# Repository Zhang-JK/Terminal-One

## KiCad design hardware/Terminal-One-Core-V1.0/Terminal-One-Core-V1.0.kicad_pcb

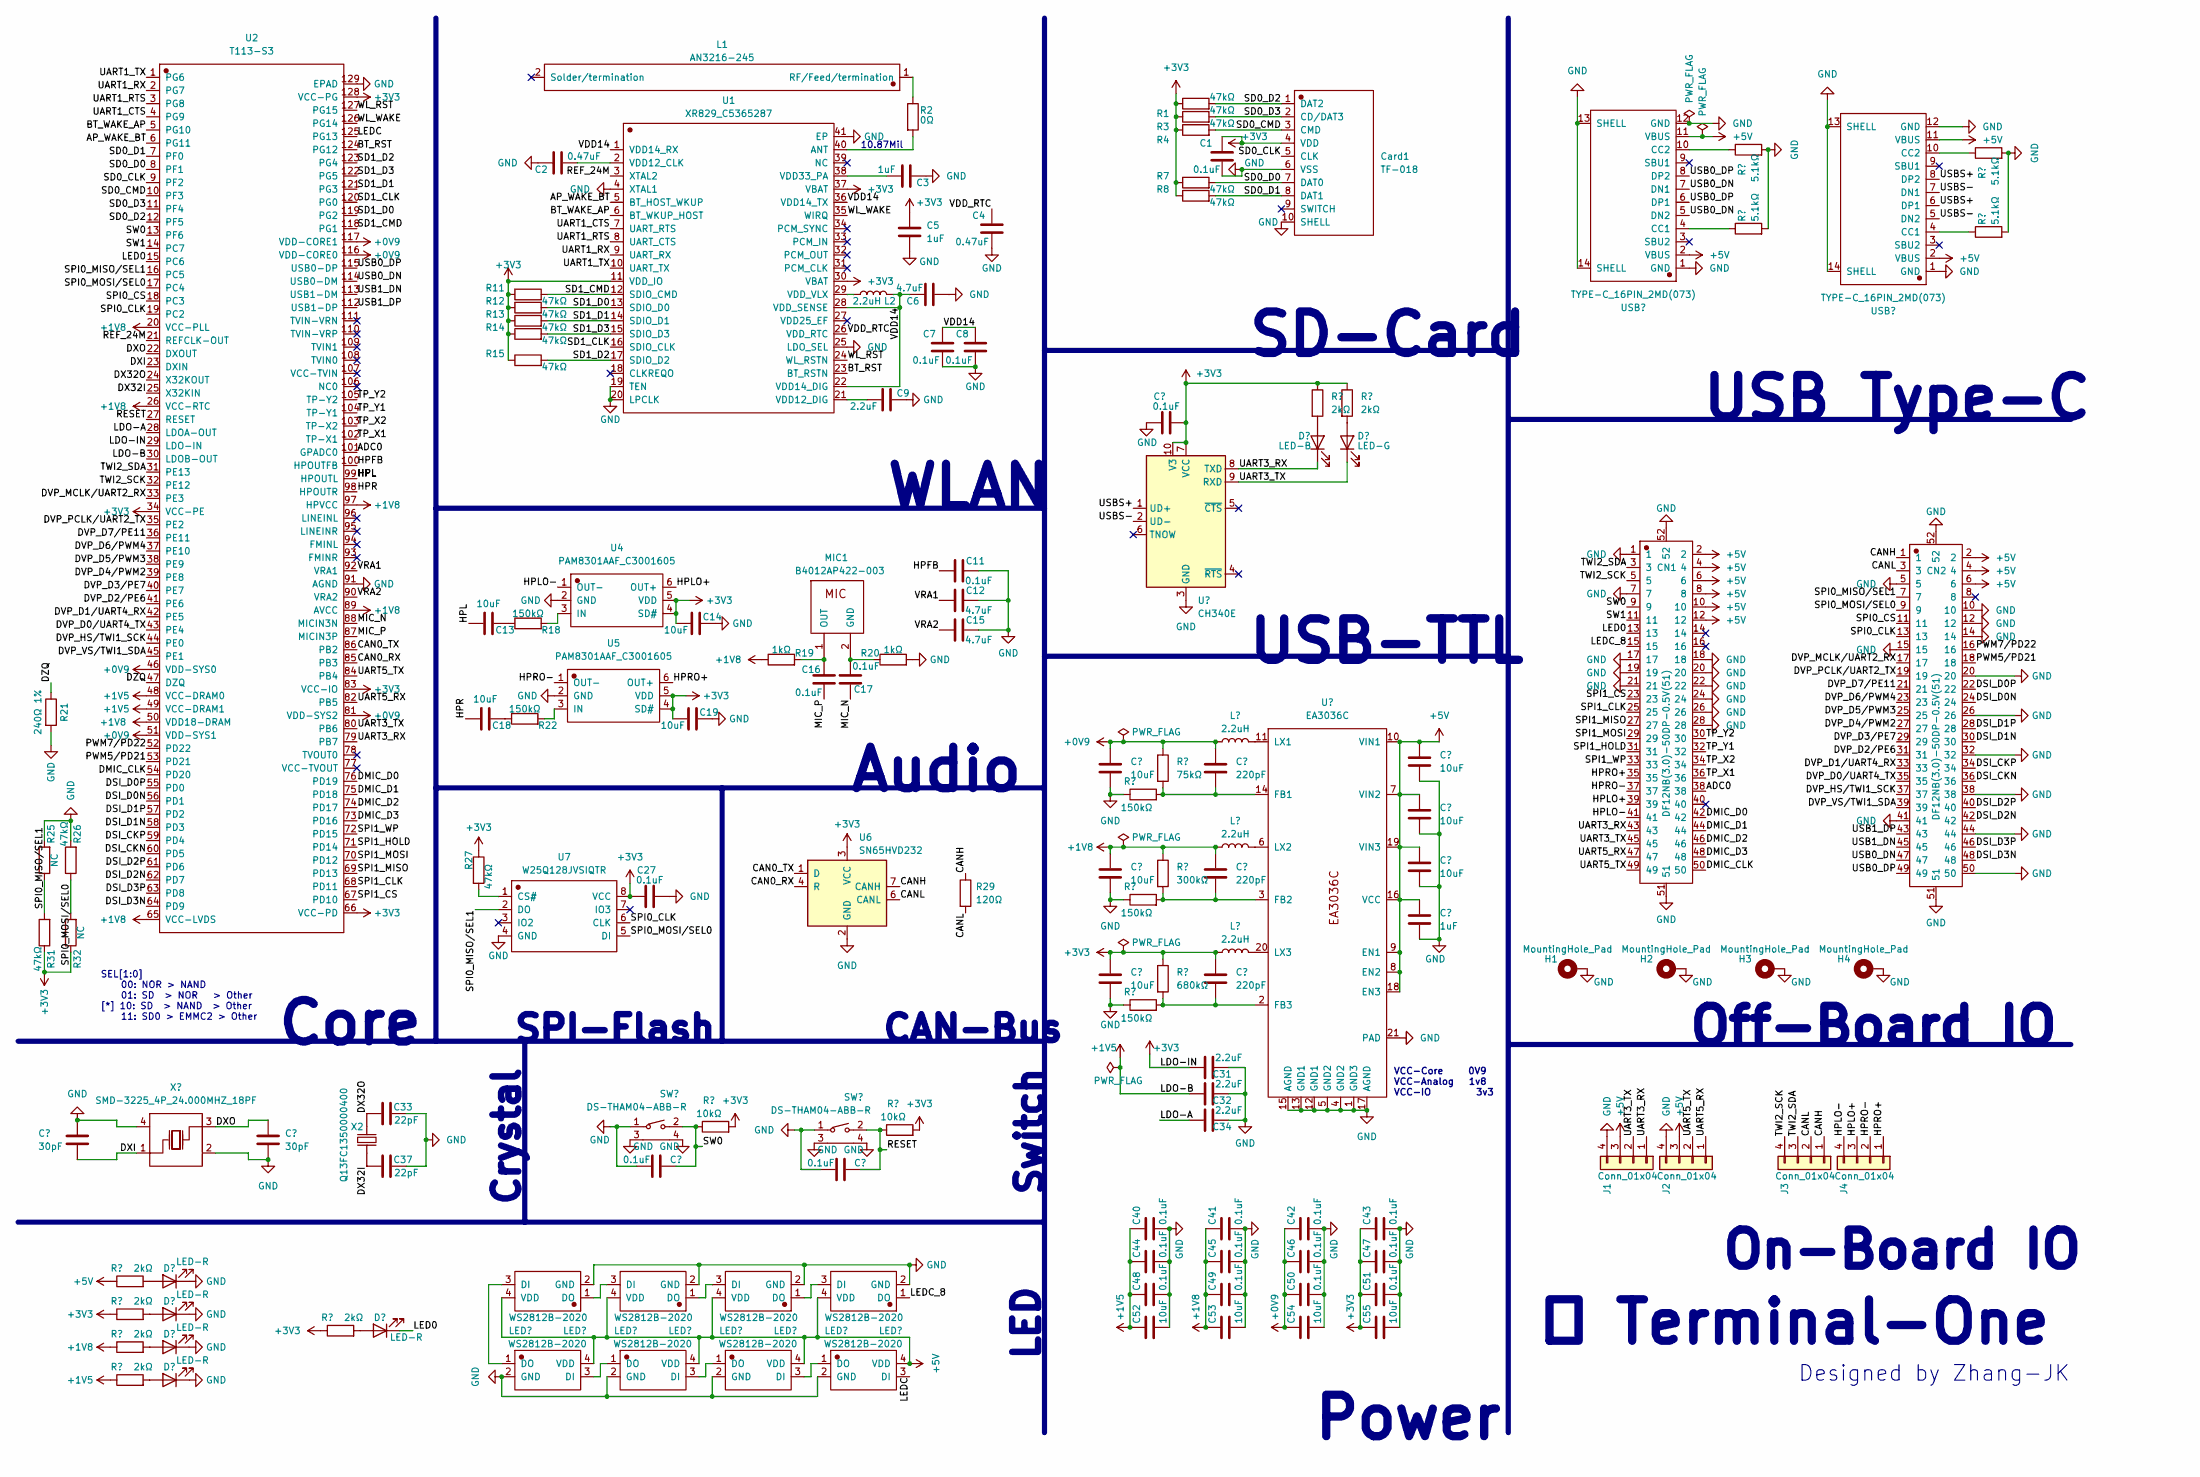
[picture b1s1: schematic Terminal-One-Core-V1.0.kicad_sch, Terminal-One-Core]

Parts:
C1, C7, C8, C10, C11, C16, C17, C27, C38, C39, C40, C41, C42, C43, C44, C45, C46, C47, C48, C49, C50, C51: 0.1uF; C_0402_1005Metric
C2, C4: 0.47uF; C_0402_1005Metric
C3, C5, C28: 1uF; C_0402_1005Metric
C6, C12, C15: 4.7uF; C_0603_1608Metric
C9, C31, C32, C34: 2.2uF; C_0603_1608Metric
C13, C14, C18, C19, C20, C23, C24, C52, C53, C54, C55: 10uF; C_0603_1608Metric
C21, C25, C29: 10uF; C_0805_2012Metric
C22, C26, C30: 220pF; C_0603_1608Metric
C33, C37: 22pF; C_0402_1005Metric
C35, C36: 30pF; C_0402_1005Metric
CN1, CN2: DF12NB(3.0)-50DP-0.5V(51); CONN-SMD_50P-P0.50_DF12NB3.0-50DP-0.5V-51
Card1: TF-018; TF-SMD_TF-018
D1: LED-B; LED_0603_1608Metric
D2: LED-G; LED_0603_1608Metric
D3, D4, D5, D6, D7: LED-R; LED_0603_1608Metric
H1, H2, H3, H4: MountingHole_Pad; MountingHole_2.7mm_M2.5_ISO14580_Pad_TopOnly
J1, J2, J3, J4: Conn_01x04; JST_GH_BM04B-GHS-TBT_1x04-1MP_P1.25mm_Vertical
L1: AN3216-245; ANT-SMD_L3.2-W1.6-A
L2, L3, L4, L5: 2.2uH; L_0805_2012Metric
LED1, LED2, LED3, LED4, LED5, LED6, LED7, LED8: WS2812B-2020; LED-SMD_4P-L2.0-W2.0-TL_WS2812B-2020
MIC1: B4012AP422-003; MIC-TH_BD4.0-P1.40-D0.3-L
R1, R3, R4, R7, R8, R11, R12, R13, R14, R15, R26, R27, R31: 47kΩ; R_0402_1005Metric
R2: 0Ω; R_0402_1005Metric
R5, R6, R9, R10: 5.1kΩ; R_0402_1005Metric
R16, R17, R37, R38, R39, R40, R41: 2kΩ; R_0402_1005Metric
R18, R22, R24, R30, R34: 150kΩ; R_0402_1005Metric
R19, R20: 1kΩ; R_0402_1005Metric
R21: 240Ω 1%; R_0402_1005Metric
R23: 75kΩ; R_0402_1005Metric
R25, R32: NC; R_0402_1005Metric
R28: 300kΩ; R_0402_1005Metric
R29: 120Ω; R_0402_1005Metric
R33: 680kΩ; R_0402_1005Metric
R35, R36: 10kΩ; R_0402_1005Metric
SW1, SW2: DS-THAM04-ABB-R; SW-SMD_D-SWITCH_DS-THAM04-ABB-R
U1: XR829_C5365287; QFN-40_L5.0-W5.0-P0.40-BL-EP3.4
U2: T113-S3; TQFP-128_L14.0-W14.0-P0.40-LS16.0-BL-EP6.4
U3: CH340E; MSOP-10_3x3mm_P0.5mm
U4, U5: PAM8301AAF_C3001605; SOT-23-6_L2.9-W1.6-P0.95-LS2.8-BR
U6: SN65HVD232; SOIC-8_3.9x4.9mm_P1.27mm
U7: W25Q128JVSIQTR; SOIC-8_L5.3-W5.3-P1.27-LS8.0-BL
U8: EA3036C; WQFN-20-1EP_3x3mm_P0.4mm_EP1.7x1.7mm_ThermalVias
USB1, USB2: TYPE-C_16PIN_2MD(073); USB-C-SMD_TYPE-C-6PIN-2MD-073
X1: SMD-3225_4P_24.000MHZ_18PF; CRYSTAL-SMD_4P-L3.2-W2.5-BL
X2: Q13FC1350000400; FC-135R_L3.2-W1.5

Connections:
+0V9: C21.1, C22.1, C42.1, C46.1, C50.1, C54.1, L3.1, R23.1, U2.46 (VDD-SYS0), U2.51 (VDD-SYS1), U2.81 (VDD-SYS2), U2.116 (VDD-CORE0), U2.117 (VDD-CORE1); also elsewhere on the board
+1V5: C32.1, C40.1, C44.1, C48.1, C52.1, R41.1, U2.30 (LDOB-OUT), U2.48 (VCC-DRAM0), U2.49 (VCC-DRAM1); also elsewhere on the board
+1V8: C25.1, C26.1, C41.1, C45.1, C49.1, C53.1, L4.1, R19.1, R28.1, R40.1, U2.20 (VCC-PLL), U2.26 (VCC-RTC), U2.50 (VDD18-DRAM), U2.65 (VCC-LVDS), U2.89 (AVCC), U2.97 (HPVCC); also elsewhere on the board
+3V3: C1.1, C5.1, C10.2, C14.1, C19.1, C27.1, C29.1, C30.1, C31.1, C43.1, C47.1, C51.1, C55.1, Card1.4 (VDD), L5.1, R1.1, R3.1, R4.1, R7.1, R8.1, R11.1, R12.1, R13.1, R14.1, R15.1, R16.1, R17.1, R27.1, R31.1, R32.1, R33.1, R35.2, R36.2, R38.1, R39.1, U1.11 (VDD_IO), U1.30 (VBAT), U1.37 (VBAT), U2.29 (LDO-IN), U2.34 (VCC-PE), U2.66 (VCC-PD), U2.83 (VCC-IO), U2.128 (VCC-PG), U3.7 (VCC), U3.10 (V3), U4.4 (SD#), U4.5 (VDD), U5.4 (SD#), U5.5 (VDD), U6.3 (VCC), U7.8 (VCC); also elsewhere on the board
+5V: C20.1, C23.1, C24.1, C28.1, CN1.2, CN1.4, CN1.6, CN1.8, CN1.10, CN1.12, CN2.2, CN2.4, CN2.6, J1.3, J2.3, LED1.4 (VDD), LED2.4 (VDD), LED3.4 (VDD), LED4.4 (VDD), LED5.4 (VDD), LED6.4 (VDD), LED7.4 (VDD), LED8.4 (VDD), R37.1, U8.7 (VIN2), U8.8 (EN2), U8.9 (EN1), U8.10 (VIN1), U8.16 (VCC), U8.18 (EN3), U8.19 (VIN3), USB1.2 (VBUS), USB1.11 (VBUS), USB2.2 (VBUS), USB2.11 (VBUS)
/ADC0: CN1.38, U2.101 (GPADC0); also elsewhere on the board
/AP_WAKE_BT: U1.5 (BT_HOST_WKUP), U2.6 (PG11); also elsewhere on the board
/BT_RST: U1.23 (BT_RSTN), U2.124 (PG12); also elsewhere on the board
/BT_WAKE_AP: U1.6 (BT_WKUP_HOST), U2.5 (PG10); also elsewhere on the board
/CAN0_RX: U2.85 (PB3), U6.4 (R); also elsewhere on the board
/CAN0_TX: U2.86 (PB2), U6.1 (D); also elsewhere on the board
/CANH: CN2.1, J3.1, R29.1, U6.7 (CANH)
/CANL: CN2.3, J3.2, R29.2, U6.6 (CANL)
/DMIC_CLK: CN1.50, U2.54 (PD20); also elsewhere on the board
/DMIC_D0: CN1.42, U2.76 (PD19); also elsewhere on the board
/DMIC_D1: CN1.44, U2.75 (PD18); also elsewhere on the board
/DMIC_D2: CN1.46, U2.74 (PD17); also elsewhere on the board
/DMIC_D3: CN1.48, U2.73 (PD16); also elsewhere on the board
/DSI_CKN: CN2.36, U2.60 (PD5); also elsewhere on the board
/DSI_CKP: CN2.34, U2.59 (PD4); also elsewhere on the board
/DSI_D0N: CN2.24, U2.56 (PD1); also elsewhere on the board
/DSI_D0P: CN2.22, U2.55 (PD0); also elsewhere on the board
/DSI_D1N: CN2.30, U2.58 (PD3); also elsewhere on the board
/DSI_D1P: CN2.28, U2.57 (PD2); also elsewhere on the board
/DSI_D2N: CN2.42, U2.62 (PD7); also elsewhere on the board
/DSI_D2P: CN2.40, U2.61 (PD6); also elsewhere on the board
/DSI_D3N: CN2.48, U2.64 (PD9); also elsewhere on the board
/DSI_D3P: CN2.46, U2.63 (PD8); also elsewhere on the board
/DVP_D0/UART4_TX: CN2.35, U2.43 (PE4); also elsewhere on the board
/DVP_D1/UART4_RX: CN2.33, U2.42 (PE5); also elsewhere on the board
/DVP_D2/PE6: CN2.31, U2.41 (PE6); also elsewhere on the board
/DVP_D3/PE7: CN2.29, U2.40 (PE7); also elsewhere on the board
/DVP_D4/PWM2: CN2.27, U2.39 (PE8); also elsewhere on the board
/DVP_D5/PWM3: CN2.25, U2.38 (PE9); also elsewhere on the board
/DVP_D6/PWM4: CN2.23, U2.37 (PE10); also elsewhere on the board
/DVP_D7/PE11: CN2.21, U2.36 (PE11); also elsewhere on the board
/DVP_HS/TWI1_SCK: CN2.37, U2.44 (PE0); also elsewhere on the board
/DVP_MCLK/UART2_RX: CN2.17, U2.33 (PE3); also elsewhere on the board
/DVP_PCLK/UART2_TX: CN2.19, U2.35 (PE2); also elsewhere on the board
/DVP_VS/TWI1_SDA: CN2.39, U2.45 (PE1); also elsewhere on the board
/DX32I: C37.1, U2.25 (X32KIN), X2.1; also elsewhere on the board
/DX32O: C33.1, U2.24 (X32KOUT), X2.2; also elsewhere on the board
/DXI: C35.2, U2.23 (DXIN), X1.1 (OSC1); also elsewhere on the board
/DXO: C36.1, U2.22 (DXOUT), X1.3 (OSC2); also elsewhere on the board
/DZQ: R21.1, U2.47 (DZQ); also elsewhere on the board
/HPFB: C11.1, U2.100 (HPOUTFB); also elsewhere on the board
/HPL: C13.2, U2.99 (HPOUTL); also elsewhere on the board
/HPLO+: CN1.39, J4.3, U4.6 (OUT+)
/HPLO-: CN1.41, J4.4, U4.1 (OUT-)
/HPR: C18.2, U2.98 (HPOUTR); also elsewhere on the board
/HPRO+: CN1.35, J4.1, U5.6 (OUT+)
/HPRO-: CN1.37, J4.2, U5.1 (OUT-)
/LDO-A: C34.1, U2.28 (LDOA-OUT); also elsewhere on the board
/LED0: CN1.13, D5.1 (K), U2.15 (PC6); also elsewhere on the board
/LEDC: LED8.3 (DI), U2.125 (PG13); also elsewhere on the board
/LEDC_8: CN1.15, LED4.1 (DO)
/MIC_N: C17.2, U2.88 (MICIN3N); also elsewhere on the board
/MIC_P: C16.1, U2.87 (MICIN3P); also elsewhere on the board
/PWM5/PD21: CN2.18, U2.53 (PD21); also elsewhere on the board
/PWM7/PD22: CN2.16, U2.52 (PD22); also elsewhere on the board
/REF_24M: U1.3 (XTAL2), U2.21 (REFCLK-OUT); also elsewhere on the board
/RESET: C39.2, R36.1, SW2.2, U2.27 (RESET); also elsewhere on the board
/SD0_CLK: Card1.5 (CLK), U2.9 (PF2); also elsewhere on the board
/SD0_CMD: Card1.3 (CMD), R4.2, U2.10 (PF3); also elsewhere on the board
/SD0_D0: Card1.7 (DAT0), R7.2, U2.8 (PF1); also elsewhere on the board
/SD0_D1: Card1.8 (DAT1), R8.2, U2.7 (PF0); also elsewhere on the board
/SD0_D2: Card1.1 (DAT2), R1.2, U2.12 (PF5); also elsewhere on the board
/SD0_D3: Card1.2 (CD/DAT3), R3.2, U2.11 (PF4); also elsewhere on the board
/SD1_CLK: U1.16 (SDIO_CLK), U2.120 (PG0); also elsewhere on the board
/SD1_CMD: R11.2, U1.12 (SDIO_CMD), U2.118 (PG1); also elsewhere on the board
/SD1_D0: R12.2, U1.13 (SDIO_D0), U2.119 (PG2); also elsewhere on the board
/SD1_D1: R13.2, U1.14 (SDIO_D1), U2.121 (PG3); also elsewhere on the board
/SD1_D2: R15.2, U1.17 (SDIO_D2), U2.123 (PG4); also elsewhere on the board
/SD1_D3: R14.2, U1.15 (SDIO_D3), U2.122 (PG5); also elsewhere on the board
/SPI0_CLK: CN2.13, U2.19 (PC2), U7.6 (CLK); also elsewhere on the board
/SPI0_CS: CN2.11, U2.18 (PC3); also elsewhere on the board
/SPI0_MISO/SEL1: CN2.7, R25.1, R31.2, U2.16 (PC5), U7.2 (DO); also elsewhere on the board
/SPI0_MOSI/SEL0: CN2.9, R26.1, R32.2, U2.17 (PC4), U7.5 (DI); also elsewhere on the board
/SPI1_CLK: CN1.25, U2.68 (PD11); also elsewhere on the board
/SPI1_CS: CN1.23, U2.67 (PD10); also elsewhere on the board
/SPI1_HOLD: CN1.31, U2.71 (PD14); also elsewhere on the board
/SPI1_MISO: CN1.27, U2.69 (PD13); also elsewhere on the board
/SPI1_MOSI: CN1.29, U2.70 (PD12); also elsewhere on the board
/SPI1_WP: CN1.33, U2.72 (PD15); also elsewhere on the board
/SW0: C38.2, CN1.9, R35.1, SW1.2, U2.13 (PF6); also elsewhere on the board
/SW1: CN1.11, U2.14 (PC7); also elsewhere on the board
/TP_X1: CN1.36, U2.102 (TP-X1); also elsewhere on the board
/TP_X2: CN1.34, U2.103 (TP-X2); also elsewhere on the board
/TP_Y1: CN1.32, U2.104 (TP-Y1); also elsewhere on the board
/TP_Y2: CN1.30, U2.105 (TP-Y2); also elsewhere on the board
/TWI2_SCK: CN1.5, J3.4, U2.32 (PE12); also elsewhere on the board
/TWI2_SDA: CN1.3, J3.3, U2.31 (PE13); also elsewhere on the board
/UART1_CTS: U1.7 (UART_RTS), U2.4 (PG9); also elsewhere on the board
/UART1_RTS: U1.8 (UART_CTS), U2.3 (PG8); also elsewhere on the board
/UART1_RX: U1.9 (UART_RX), U2.2 (PG7); also elsewhere on the board
/UART1_TX: U1.10 (UART_TX), U2.1 (PG6); also elsewhere on the board
/UART3_RX: CN1.43, D1.1 (K), J1.1, U2.79 (PB7), U3.8 (TXD); also elsewhere on the board
/UART3_TX: CN1.45, D2.1 (K), J1.2, U2.80 (PB6), U3.9 (RXD); also elsewhere on the board
/UART5_RX: CN1.47, J2.1, U2.82 (PB5); also elsewhere on the board
/UART5_TX: CN1.49, J2.2, U2.84 (PB4); also elsewhere on the board
/USB0_DN: CN2.47, U2.114 (USB0-DM), USB1.5 (DN2), USB1.7 (DN1); also elsewhere on the board
/USB0_DP: CN2.49, U2.115 (USB0-DP), USB1.6 (DP1), USB1.8 (DP2); also elsewhere on the board
/USB1_DN: CN2.45, U2.113 (USB1-DM); also elsewhere on the board
/USB1_DP: CN2.43, U2.112 (USB1-DP); also elsewhere on the board
/USBS+: U3.1 (UD+), USB2.6 (DP1), USB2.8 (DP2)
/USBS-: U3.2 (UD-), USB2.5 (DN2), USB2.7 (DN1)
/VDD14: C6.1, C7.2, C8.2, L2.2, U1.1 (VDD14_RX), U1.22 (VDD14_DIG), U1.28 (VDD_SENSE), U1.36 (VDD14_TX)
/VDD_RTC: C4.2, U1.26 (VDD_RTC)
/VRA1: C12.1, U2.92 (VRA1); also elsewhere on the board
/VRA2: C15.1, U2.90 (VRA2); also elsewhere on the board
/WL_RST: U1.24 (WL_RSTN), U2.127 (PG15); also elsewhere on the board
/WL_WAKE: U1.35 (WIRQ), U2.126 (PG14); also elsewhere on the board
GND: C1.2, C2.2, C3.2, C4.1, C5.2, C6.2, C7.1, C8.1, C9.1, C10.1, C11.2, C12.2, C14.2, C15.2, C19.2, C20.2, C21.2, C23.2, C24.2, C25.2, C27.2, C28.2, C29.2, C31.2, C32.2, C33.2, C34.2, C35.1, C36.2, C37.2, C38.1, C39.1, C40.2, C41.2, C42.2, C43.2, C44.2, C45.2, C46.2, C47.2, C48.2, C49.2, C50.2, C51.2, C52.2, C53.2, C54.2, C55.2, CN1.1, CN1.7, CN1.17, CN1.18, CN1.19, CN1.20, CN1.21, CN1.22, CN1.24, CN1.26, CN1.28, CN1.51, CN1.52, CN2.5, CN2.10, CN2.12, CN2.14, CN2.15, CN2.20, CN2.26, CN2.32, CN2.38, CN2.41, CN2.44, CN2.50, CN2.51, CN2.52, Card1.6 (VSS), Card1.10 (SHELL), D3.1 (K), D4.1 (K), D6.1 (K), D7.1 (K), H1.1, H2.1, H3.1, H4.1, J1.4, J2.4, LED1.2 (GND), LED2.2 (GND), LED3.2 (GND), LED4.2 (GND), LED5.2 (GND), LED6.2 (GND), LED7.2 (GND), LED8.2 (GND), R5.2, R6.2, R9.2, R10.2, R20.2, R21.2, R24.1, R25.2, R26.2, R30.1, R34.1, SW1.1, SW1.3, SW1.4, SW2.1, SW2.3, SW2.4, U1.4 (XTAL1), U1.19 (TEN), U1.20 (LPCLK), U1.25 (LDO_SEL), U1.41 (EP), U2.91 (AGND), U2.129 (EPAD), U3.3 (GND), U4.2 (GND), U5.2 (GND), U6.2 (GND), U7.4 (GND), U8.1 (GND3), U8.4 (GND2), U8.5 (GND2), U8.12 (GND1), U8.13 (GND1), U8.15 (AGND), U8.17 (AGND), U8.21 (PAD), USB1.1 (GND), USB1.12 (GND), USB1.13 (SHELL), USB1.14 (SHELL), USB2.1 (GND), USB2.12 (GND), USB2.13 (SHELL), USB2.14 (SHELL), X1.2 (GND), X1.4 (GND); also elsewhere on the board
unnamed: C13.1, R18.1
unnamed: C18.1, R22.1
unnamed: D1.2 (A), R16.2
unnamed: D2.2 (A), R17.2
unnamed: D3.2 (A), R37.2
unnamed: D4.2 (A), R38.2
unnamed: D5.2 (A), R39.2
unnamed: D6.2 (A), R40.2
unnamed: D7.2 (A), R41.2
unnamed: L1.1 (RF/Feed/termination), R2.1
unnamed: LED1.3 (DI), LED5.1 (DO)
unnamed: LED1.1 (DO), LED2.3 (DI)
unnamed: LED2.1 (DO), LED3.3 (DI)
unnamed: LED3.1 (DO), LED4.3 (DI)
unnamed: LED5.3 (DI), LED6.1 (DO)
unnamed: LED6.3 (DI), LED7.1 (DO)
unnamed: LED7.3 (DI), LED8.1 (DO)
unnamed: C17.1, MIC1.2 (GND), R20.1
unnamed: C16.2, MIC1.1 (OUT), R19.2
unnamed: R2.2, U1.40 (ANT)
unnamed: C2.1, U1.2 (VDD12_CLK)
unnamed: C9.2, U1.21 (VDD12_DIG)
unnamed: C3.1, U1.38 (VDD33_PA)
unnamed: L2.1, U1.29 (VDD_VLX)
unnamed: R18.2, U4.3 (IN)
unnamed: R22.2, U5.3 (IN)
unnamed: R27.2, U7.1 (CS#)
unnamed: C22.2, R23.2, R24.2, U8.14 (FB1)
unnamed: C26.2, R28.2, R30.2, U8.3 (FB2)
unnamed: C30.2, R33.2, R34.2, U8.2 (FB3)
unnamed: L3.2, U8.11 (LX1)
unnamed: L4.2, U8.6 (LX2)
unnamed: L5.2, U8.20 (LX3)
unnamed: R9.1, USB1.4 (CC1)
unnamed: R5.1, USB1.10 (CC2)
unnamed: R10.1, USB2.4 (CC1)
unnamed: R6.1, USB2.10 (CC2)

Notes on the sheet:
Audio
CAN-Bus
Off-Board IO
USB-TTL
Switch
LED
USB Type-C
Designed by Zhang-JK
WLAN
 Terminal-One
Power
SPI-Flash
Core
Crystal
SD-Card
10.87Mil
On-Board IO
SEL[1:0] 00: NOR > NAND 01: SD > NOR > Other [*] 10: SD > NAND > Other 11: SD0 > EMMC2 > Other
VCC-Core 0V9 VCC-Analog 1v8 VCC-IO 3v3

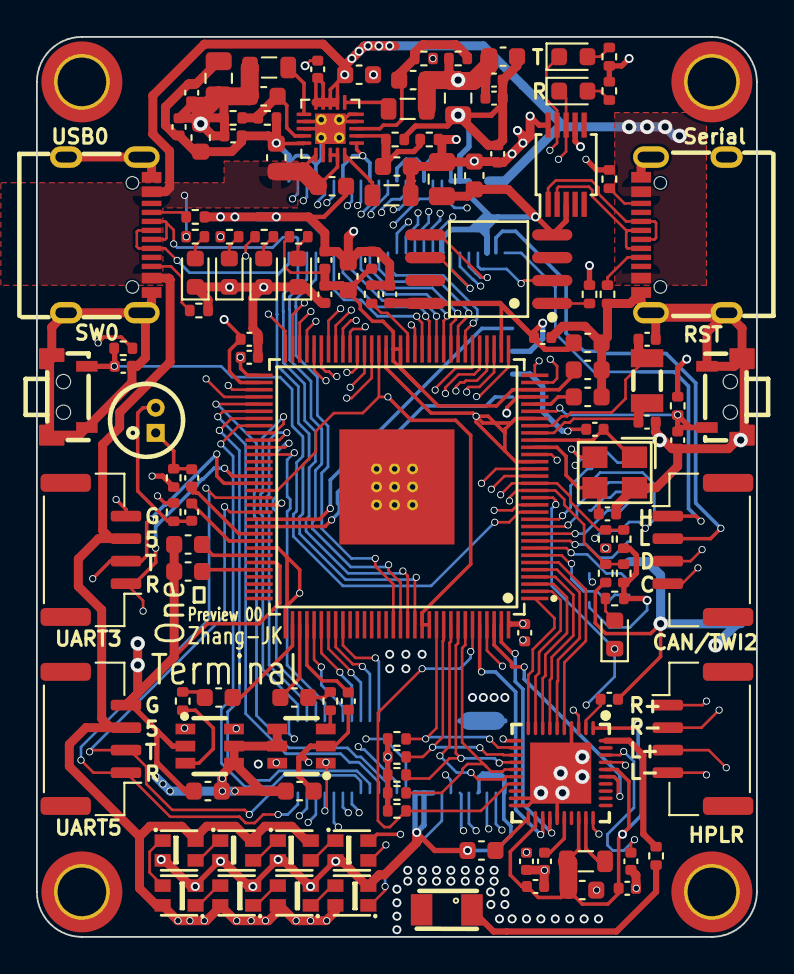
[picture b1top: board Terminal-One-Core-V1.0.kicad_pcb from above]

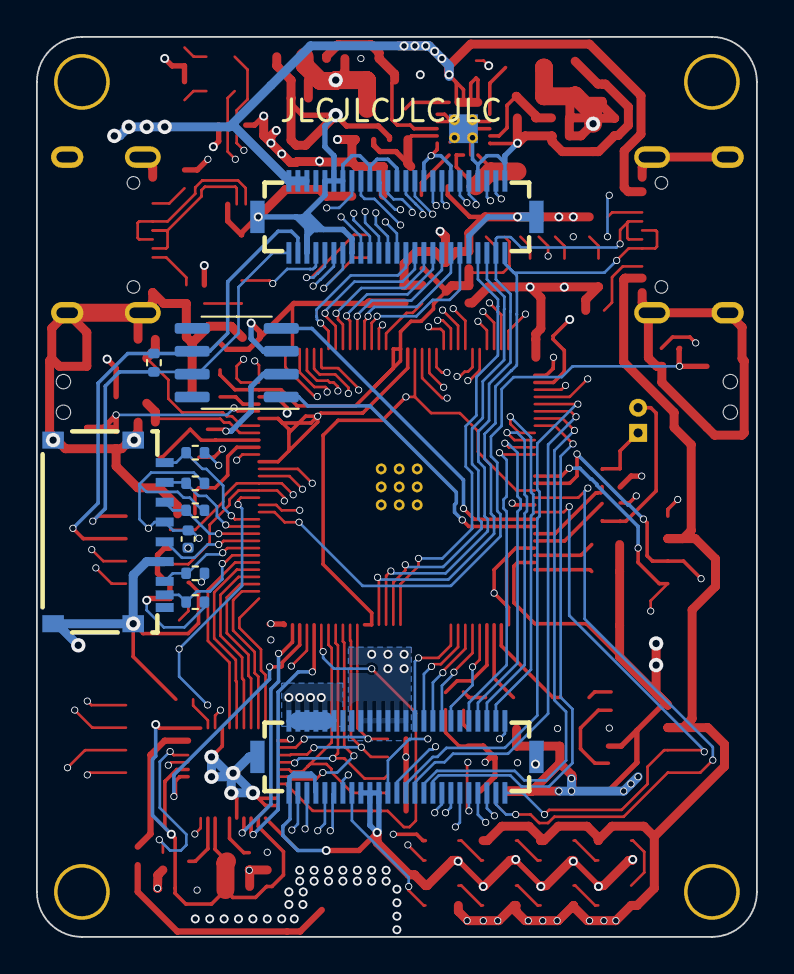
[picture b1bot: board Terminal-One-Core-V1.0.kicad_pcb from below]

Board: 4 copper layers, 40.0 x 50.0 mm, 142 parts (11 on the bottom side), 150 nets.

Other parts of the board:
Ur: T113-S3; TQFP-128_L14.0-W14.0-P0.40-LS16.0-BL-EP6.4

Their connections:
+0V9: Ur.46 (VDD-SYS0), Ur.51 (VDD-SYS1), Ur.81 (VDD-SYS2), Ur.116 (VDD-CORE0), Ur.117 (VDD-CORE1); also elsewhere on the board
+1V5: Ur.30 (LDOB-OUT), Ur.48 (VCC-DRAM0), Ur.49 (VCC-DRAM1); also elsewhere on the board
+1V8: Ur.20 (VCC-PLL), Ur.26 (VCC-RTC), Ur.50 (VDD18-DRAM), Ur.65 (VCC-LVDS), Ur.89 (AVCC), Ur.97 (HPVCC); also elsewhere on the board
+3V3: Ur.29 (LDO-IN), Ur.34 (VCC-PE), Ur.66 (VCC-PD), Ur.83 (VCC-IO), Ur.128 (VCC-PG); also elsewhere on the board
/ADC0: Ur.101 (GPADC0); also elsewhere on the board
/AP_WAKE_BT: Ur.6 (PG11); also elsewhere on the board
/BT_RST: Ur.124 (PG12); also elsewhere on the board
/BT_WAKE_AP: Ur.5 (PG10); also elsewhere on the board
/CAN0_RX: Ur.85 (PB3); also elsewhere on the board
/CAN0_TX: Ur.86 (PB2); also elsewhere on the board
/DMIC_CLK: Ur.54 (PD20); also elsewhere on the board
/DMIC_D0: Ur.76 (PD19); also elsewhere on the board
/DMIC_D1: Ur.75 (PD18); also elsewhere on the board
/DMIC_D2: Ur.74 (PD17); also elsewhere on the board
/DMIC_D3: Ur.73 (PD16); also elsewhere on the board
/DSI_CKN: Ur.60 (PD5); also elsewhere on the board
/DSI_CKP: Ur.59 (PD4); also elsewhere on the board
/DSI_D0N: Ur.56 (PD1); also elsewhere on the board
/DSI_D0P: Ur.55 (PD0); also elsewhere on the board
/DSI_D1N: Ur.58 (PD3); also elsewhere on the board
/DSI_D1P: Ur.57 (PD2); also elsewhere on the board
/DSI_D2N: Ur.62 (PD7); also elsewhere on the board
/DSI_D2P: Ur.61 (PD6); also elsewhere on the board
/DSI_D3N: Ur.64 (PD9); also elsewhere on the board
/DSI_D3P: Ur.63 (PD8); also elsewhere on the board
/DVP_D0/UART4_TX: Ur.43 (PE4); also elsewhere on the board
/DVP_D1/UART4_RX: Ur.42 (PE5); also elsewhere on the board
/DVP_D2/PE6: Ur.41 (PE6); also elsewhere on the board
/DVP_D3/PE7: Ur.40 (PE7); also elsewhere on the board
/DVP_D4/PWM2: Ur.39 (PE8); also elsewhere on the board
/DVP_D5/PWM3: Ur.38 (PE9); also elsewhere on the board
/DVP_D6/PWM4: Ur.37 (PE10); also elsewhere on the board
/DVP_D7/PE11: Ur.36 (PE11); also elsewhere on the board
/DVP_HS/TWI1_SCK: Ur.44 (PE0); also elsewhere on the board
/DVP_MCLK/UART2_RX: Ur.33 (PE3); also elsewhere on the board
/DVP_PCLK/UART2_TX: Ur.35 (PE2); also elsewhere on the board
/DVP_VS/TWI1_SDA: Ur.45 (PE1); also elsewhere on the board
/DX32I: Ur.25 (X32KIN); also elsewhere on the board
/DX32O: Ur.24 (X32KOUT); also elsewhere on the board
/DXI: Ur.23 (DXIN); also elsewhere on the board
/DXO: Ur.22 (DXOUT); also elsewhere on the board
/DZQ: Ur.47 (DZQ); also elsewhere on the board
/HPFB: Ur.100 (HPOUTFB); also elsewhere on the board
/HPL: Ur.99 (HPOUTL); also elsewhere on the board
/HPR: Ur.98 (HPOUTR); also elsewhere on the board
/LDO-A: Ur.28 (LDOA-OUT); also elsewhere on the board
/LED0: Ur.15 (PC6); also elsewhere on the board
/LEDC: Ur.125 (PG13); also elsewhere on the board
/MIC_N: Ur.88 (MICIN3N); also elsewhere on the board
/MIC_P: Ur.87 (MICIN3P); also elsewhere on the board
/PWM5/PD21: Ur.53 (PD21); also elsewhere on the board
/PWM7/PD22: Ur.52 (PD22); also elsewhere on the board
/REF_24M: Ur.21 (REFCLK-OUT); also elsewhere on the board
/RESET: Ur.27 (RESET); also elsewhere on the board
/SD0_CLK: Ur.9 (PF2); also elsewhere on the board
/SD0_CMD: Ur.10 (PF3); also elsewhere on the board
/SD0_D0: Ur.8 (PF1); also elsewhere on the board
/SD0_D1: Ur.7 (PF0); also elsewhere on the board
/SD0_D2: Ur.12 (PF5); also elsewhere on the board
/SD0_D3: Ur.11 (PF4); also elsewhere on the board
/SD1_CLK: Ur.120 (PG0); also elsewhere on the board
/SD1_CMD: Ur.118 (PG1); also elsewhere on the board
/SD1_D0: Ur.119 (PG2); also elsewhere on the board
/SD1_D1: Ur.121 (PG3); also elsewhere on the board
/SD1_D2: Ur.123 (PG4); also elsewhere on the board
/SD1_D3: Ur.122 (PG5); also elsewhere on the board
/SPI0_CLK: Ur.19 (PC2); also elsewhere on the board
/SPI0_CS: Ur.18 (PC3); also elsewhere on the board
/SPI0_MISO/SEL1: Ur.16 (PC5); also elsewhere on the board
/SPI0_MOSI/SEL0: Ur.17 (PC4); also elsewhere on the board
/SPI1_CLK: Ur.68 (PD11); also elsewhere on the board
/SPI1_CS: Ur.67 (PD10); also elsewhere on the board
/SPI1_HOLD: Ur.71 (PD14); also elsewhere on the board
/SPI1_MISO: Ur.69 (PD13); also elsewhere on the board
/SPI1_MOSI: Ur.70 (PD12); also elsewhere on the board
/SPI1_WP: Ur.72 (PD15); also elsewhere on the board
/SW0: Ur.13 (PF6); also elsewhere on the board
/SW1: Ur.14 (PC7); also elsewhere on the board
/TP_X1: Ur.102 (TP-X1); also elsewhere on the board
/TP_X2: Ur.103 (TP-X2); also elsewhere on the board
/TP_Y1: Ur.104 (TP-Y1); also elsewhere on the board
/TP_Y2: Ur.105 (TP-Y2); also elsewhere on the board
/TWI2_SCK: Ur.32 (PE12); also elsewhere on the board
/TWI2_SDA: Ur.31 (PE13); also elsewhere on the board
/UART1_CTS: Ur.4 (PG9); also elsewhere on the board
/UART1_RTS: Ur.3 (PG8); also elsewhere on the board
/UART1_RX: Ur.2 (PG7); also elsewhere on the board
/UART1_TX: Ur.1 (PG6); also elsewhere on the board
/UART3_RX: Ur.79 (PB7); also elsewhere on the board
/UART3_TX: Ur.80 (PB6); also elsewhere on the board
/UART5_RX: Ur.82 (PB5); also elsewhere on the board
/UART5_TX: Ur.84 (PB4); also elsewhere on the board
/USB0_DN: Ur.114 (USB0-DM); also elsewhere on the board
/USB0_DP: Ur.115 (USB0-DP); also elsewhere on the board
/USB1_DN: Ur.113 (USB1-DM); also elsewhere on the board
/USB1_DP: Ur.112 (USB1-DP); also elsewhere on the board
/VRA1: Ur.92 (VRA1); also elsewhere on the board
/VRA2: Ur.90 (VRA2); also elsewhere on the board
/WL_RST: Ur.127 (PG15); also elsewhere on the board
/WL_WAKE: Ur.126 (PG14); also elsewhere on the board
GND: Ur.91 (AGND), Ur.129 (EPAD); also elsewhere on the board

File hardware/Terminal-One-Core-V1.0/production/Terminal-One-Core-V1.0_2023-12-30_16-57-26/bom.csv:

Designator,Footprint,Quantity,Value,LCSC Part #
"C1, C10, C11, C16, C17, C27, C38, C39, C40, C41, C42, C43, C44, C45, C46, C47, C48, C49, C50, C51, C7, C8",0402,22,0.1uF,
"C12, C15, C6",0603,3,4.7uF,
"C13, C14, C18, C19, C20, C23, C24, C52, C53, C54, C55",0603,11,10uF,
"C2, C4",0402,2,0.47uF,
"C21, C25, C29",0805,3,10uF,
"C22, C26, C30",0603,3,220pF,
"C28, C3, C5",0402,3,1uF,
"C31, C32, C34, C9",0603,4,2.2uF,
"C33, C37",0402,2,22pF,
"C35, C36",0402,2,30pF,
"CN1, CN2",CONN-SMD_50P-P0.50_DF12NB3.0-50DP-0.5V-51,2,DF12NB(3.0)-50DP-0.5V(51),
Card1,TF-SMD_TF-018,1,TF-018,
D1,0603,1,LED-B,
D2,0603,1,LED-G,
"D3, D4, D5, D6, D7",0603,5,LED-R,
"H1, H2, H3, H4",MountingHole_2.7mm_M2.5_ISO14580_Pad_TopOnly,4,MountingHole_Pad,
"J1, J2, J3, J4",JST_GH_BM04B-GHS-TBT_1x04-1MP_P1.25mm_Vertical,4,Conn_01x04,
L1,ANT-SMD_L3.2-W1.6-A,1,AN3216-245,
"L2, L3, L4, L5",0805,4,2.2uH,
"LED1, LED2, LED3, LED4, LED5, LED6, LED7, LED8",LED-SMD_4P-L2.0-W2.0-TL_WS2812B-2020,8,WS2812B-2020,
MIC1,MIC-TH_BD4.0-P1.40-D0.3-L,1,B4012AP422-003,
"R1, R11, R12, R13, R14, R15, R26, R27, R3, R31, R4, R7, R8",0402,13,47kΩ,
"R10, R5, R6, R9",0402,4,5.1kΩ,
"R16, R17, R37, R38, R39, R40, R41",0402,7,2kΩ,
"R18, R22, R24, R30, R34",0402,5,150kΩ,
"R19, R20",0402,2,1kΩ,
R2,0402,1,0Ω,
R21,0402,1,240Ω 1%,
R23,0402,1,75kΩ,
"R25, R32",0402,2,NC,
R28,0402,1,300kΩ,
R29,0402,1,120Ω,
R33,0402,1,680kΩ,
"R35, R36",0402,2,10kΩ,
"SW1, SW2",SW-SMD_D-SWITCH_DS-THAM04-ABB-R,2,DS-THAM04-ABB-R,
U1,QFN-40_L5.0-W5.0-P0.40-BL-EP3.4,1,XR829_C5365287,
U3,MSOP-10_3x3mm_P0.5mm,1,CH340E,
"U4, U5",SOT-23-6_L2.9-W1.6-P0.95-LS2.8-BR,2,PAM8301AAF_C3001605,
U6,SOIC-8_3.9x4.9mm_P1.27mm,1,SN65HVD232,
U7,SOIC-8_L5.3-W5.3-P1.27-LS8.0-BL,1,W25Q128JVSIQTR,
U8,WQFN-20-1EP_3x3mm_P0.4mm_EP1.7x1.7mm_ThermalVias,1,EA3036C,
"USB1, USB2",USB-C-SMD_TYPE-C-6PIN-2MD-073,2,TYPE-C_16PIN_2MD(073),
Ur,TQFP-128_L14.0-W14.0-P0.40-LS16.0-BL-EP6.4,1,T113-S3,
X1,CRYSTAL-SMD_4P-L3.2-W2.5-BL,1,SMD-3225_4P_24.000MHZ_18PF,
X2,FC-135R_L3.2-W1.5,1,Q13FC1350000400,

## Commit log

2024-01-20 finish first version of hardware design
